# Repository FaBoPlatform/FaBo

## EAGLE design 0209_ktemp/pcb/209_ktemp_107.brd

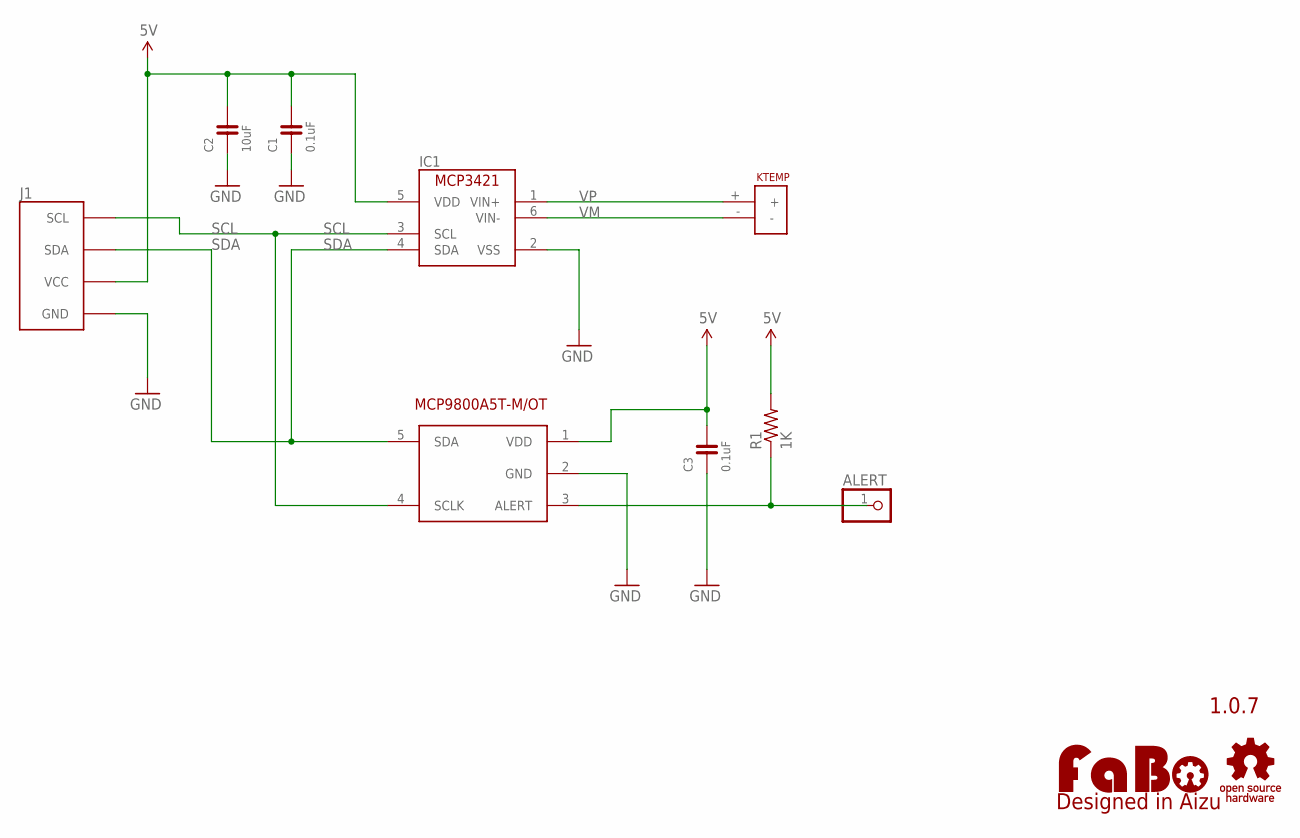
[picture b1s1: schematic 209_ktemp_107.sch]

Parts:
ALERT: PINHD-1X1; 1X01
C1, C3: 0.1uF; 0603
C2: 10uF; 0603
IC1: MCP3421; SOT-23
J1: FABO_BRICK_I2CI2C_TEMP_LOG2; FABO_BRICK_I2C_LONG2
LOGO1: LOGO_FABO-M; LOGO_FABO_M
R1: 1K; R0603
U$2: PCC-SMP-J
U$3: LOGO_OSHW-M_BOTTOM; LOGO_OSHW_M_BOTTOM
U$5: MCP9800_SOT-23; SOT23-5

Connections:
5V: C1.2, C2.2, C3.2, IC1.5 (VDD), J1.VCC, R1.2, U$5.1 (VDD)
GND: C1.1, C2.1, C3.1, IC1.2 (VSS), J1.GND, U$5.2 (GND)
unnamed: ALERT.1, R1.1, U$5.3 (ALERT)
SCL: IC1.3 (SCL), J1.SCL, U$5.4 (SCLK)
SDA: IC1.4 (SDA), J1.SDA, U$5.5 (SDA)
VM: IC1.6 (VIN-), U$2.-
VP: IC1.1 (VIN+), U$2.+

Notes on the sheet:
1.0.7

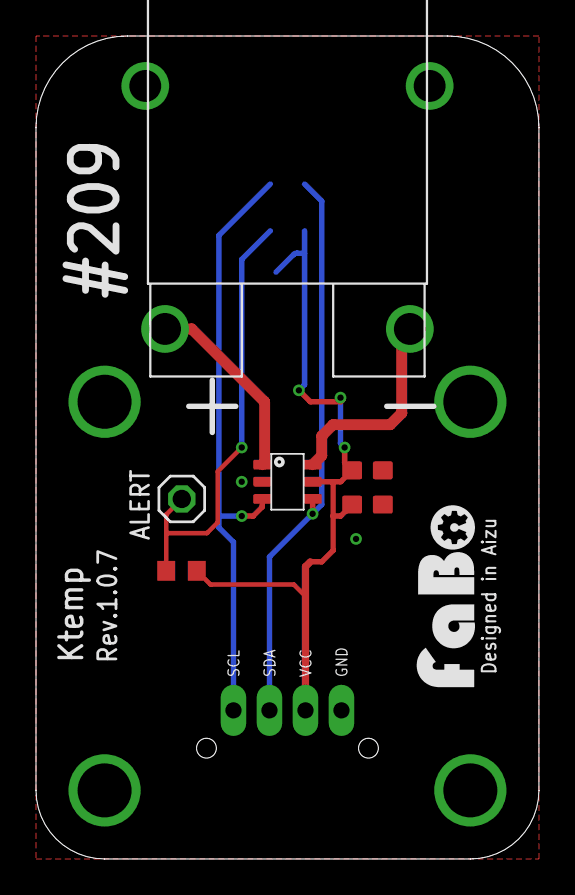
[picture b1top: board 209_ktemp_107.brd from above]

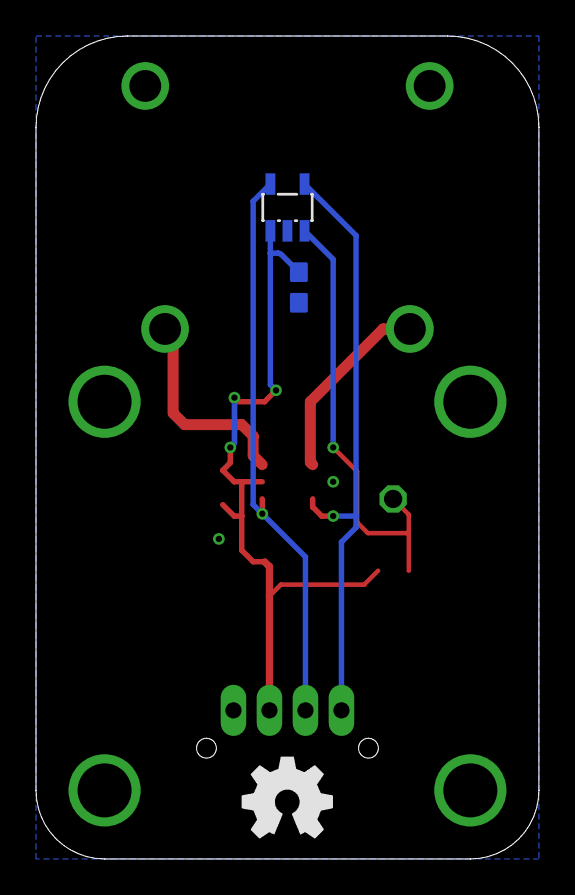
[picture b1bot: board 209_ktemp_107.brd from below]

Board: 2 copper layers, 27.9 x 45.7 mm, 11 parts (2 on the bottom side), 7 nets.

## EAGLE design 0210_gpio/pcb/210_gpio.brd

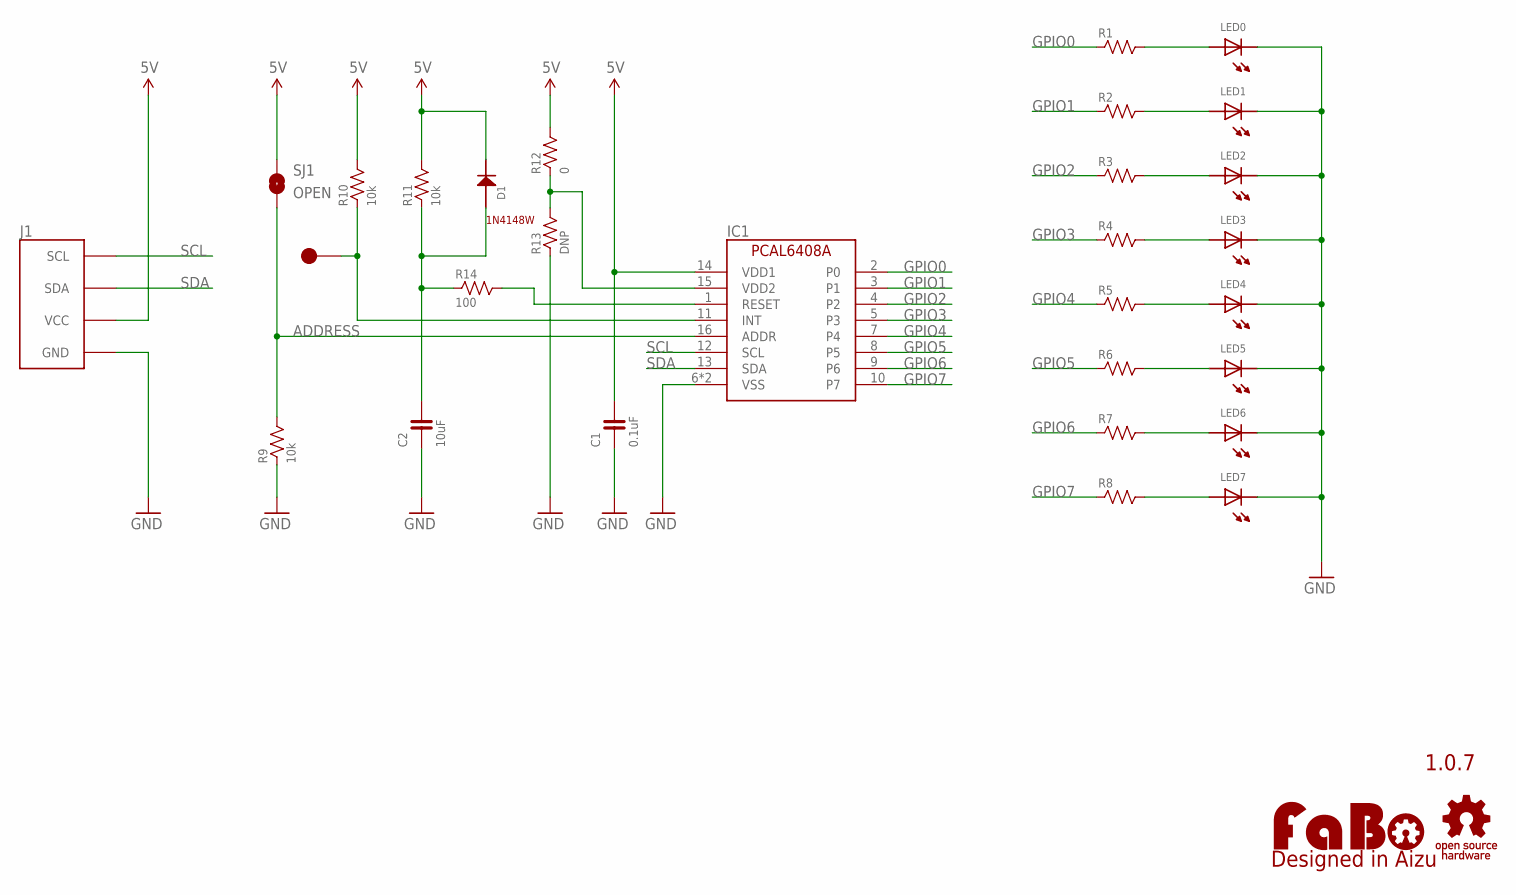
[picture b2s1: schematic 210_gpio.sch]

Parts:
C1: 0.1uF; 0603
C2: 10uF; 0805
D1: 1N4148; 1N4148W
IC1: NX-PCAL6408A; NXP-PCAL6408A
J1: FABO_BRICK_I2C
LED0, LED1, LED2, LED3, LED4, LED5, LED6, LED7: LED-0603-NARROW; 0603-NARROW
LOGO1: LOGO_FABO-M; LOGO_FABO_M
R1, R2, R3, R4, R5, R6, R7, R8: RESISTOR-0603-NARROW; 0603-NARROW
R9, R10, R11: 10k; 0603-NARROW
R12: 0; 0603-NARROW
R13: DNP; 0603-NARROW
R14: 100; 0603-NARROW
SJ1: OPEN; SMD-JUMPER-2-OPEN
TP1: TP-15
U$2: LOGO_OSHW-M_BOTTOM; LOGO_OSHW_M_BOTTOM

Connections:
5V: C1.2, D1.CATHODE, IC1.14 (VDD1), J1.VCC, R10.2, R11.2, R12.2, SJ1.1
ADDRESS: IC1.16 (ADDR), R9.2, SJ1.2
GND: C1.1, C2.1, IC1.6 (VSS), IC1.17 (VSS), J1.GND, LED0.CATHODE, LED1.CATHODE, LED2.CATHODE, LED3.CATHODE, LED4.CATHODE, LED5.CATHODE, LED6.CATHODE, LED7.CATHODE, R9.1, R13.1
GPIO0: IC1.2 (P0), R1.1
GPIO1: IC1.3 (P1), R2.1
GPIO2: IC1.4 (P2), R3.1
GPIO3: IC1.5 (P3), R4.1
GPIO4: IC1.7 (P4), R5.1
GPIO5: IC1.8 (P5), R6.1
GPIO6: IC1.9 (P6), R7.1
GPIO7: IC1.10 (P7), R8.1
unnamed: LED0.ANODE, R1.2
unnamed: LED1.ANODE, R2.2
unnamed: LED2.ANODE, R3.2
unnamed: LED3.ANODE, R4.2
unnamed: LED4.ANODE, R5.2
unnamed: LED5.ANODE, R6.2
unnamed: LED6.ANODE, R7.2
unnamed: LED7.ANODE, R8.2
unnamed: IC1.11 (INT), R10.1, TP1.1
unnamed: C2.2, D1.ANODE, R11.1, R14.1
unnamed: IC1.1 (RESET), R14.2
unnamed: IC1.15 (VDD2), R12.1, R13.2
SCL: IC1.12 (SCL), J1.SCL
SDA: IC1.13 (SDA), J1.SDA

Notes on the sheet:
1.0.7
1N4148W

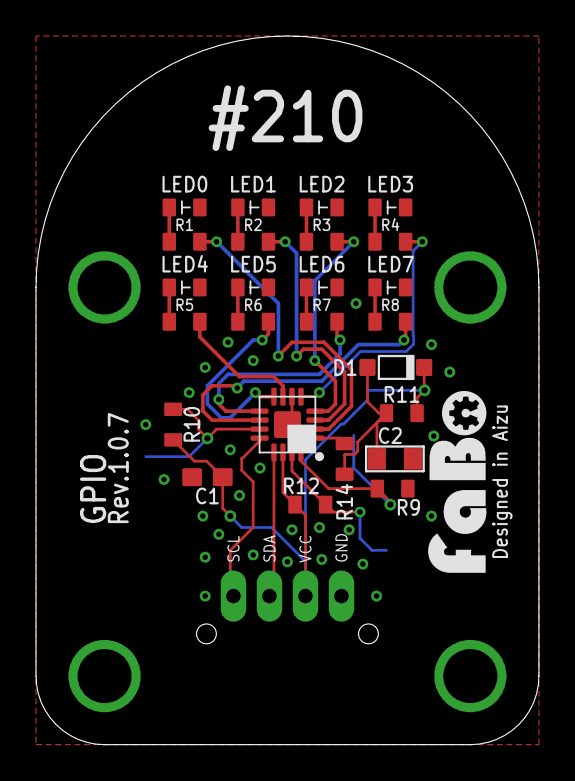
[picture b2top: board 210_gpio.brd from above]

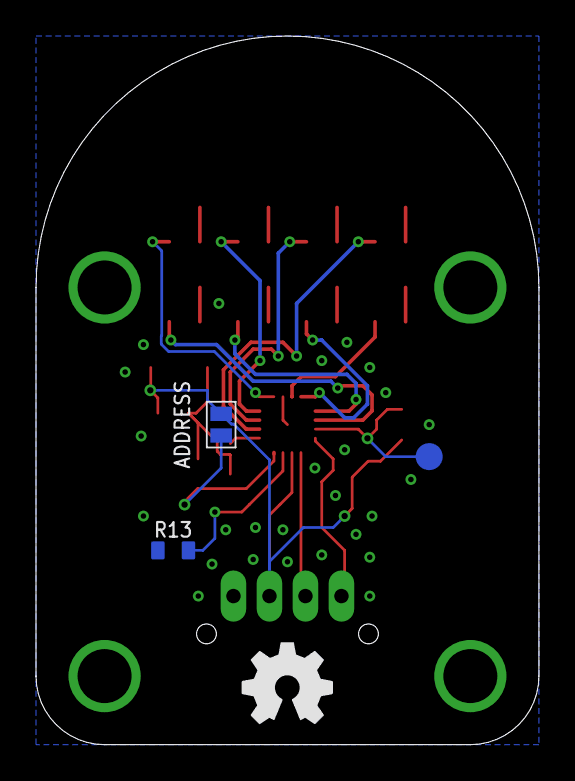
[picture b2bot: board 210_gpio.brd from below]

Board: 2 copper layers, 27.9 x 39.4 mm, 31 parts (3 on the bottom side), 25 nets.

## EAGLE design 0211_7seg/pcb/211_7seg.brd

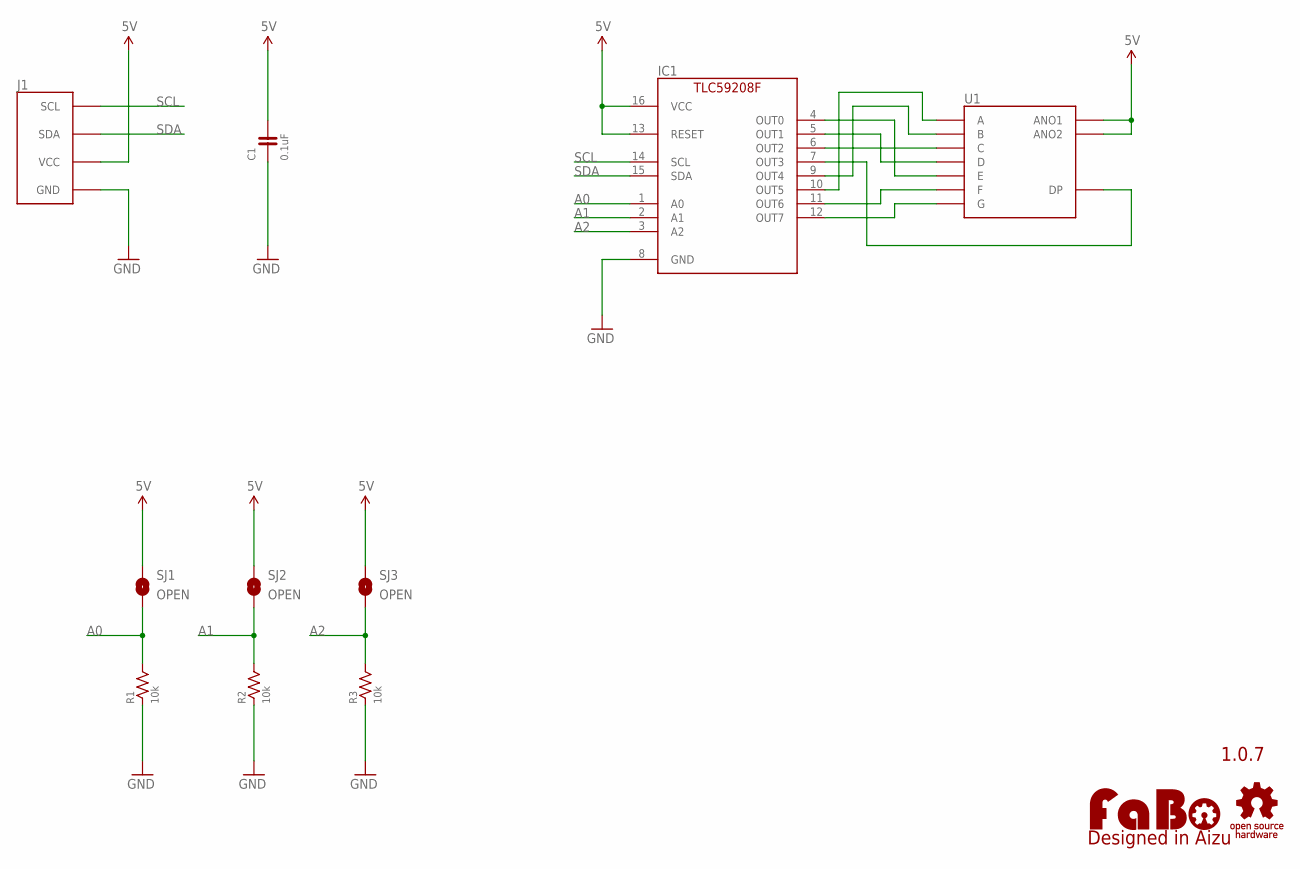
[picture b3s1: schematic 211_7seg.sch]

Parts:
C1: 0.1uF; 0603
IC1: TLC59208FIPWR; TSSOP16
J1: FABO_BRICK_I2C
LOGO1: LOGO_FABO-M; LOGO_FABO_M
R1, R2, R3: 10k; 0603
SJ1, SJ2, SJ3: OPEN; SMD-JUMPER-2-OPEN
U1: 7SEG_ANO; A-551SRD
U$2: LOGO_OSHW-M_BOTTOM; LOGO_OSHW_M_BOTTOM

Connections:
5V: C1.2, IC1.13 (RESET), IC1.16 (VCC), J1.VCC, SJ1.1, SJ2.1, SJ3.1, U1.ANO1, U1.ANO2
A0: IC1.1 (A0), R1.2, SJ1.2
A1: IC1.2 (A1), R2.2, SJ2.2
A2: IC1.3 (A2), R3.2, SJ3.2
GND: C1.1, IC1.8 (GND), J1.GND, R1.1, R2.1, R3.1
unnamed: IC1.4 (OUT0), U1.E
unnamed: IC1.5 (OUT1), U1.D
unnamed: IC1.6 (OUT2), U1.C
unnamed: IC1.7 (OUT3), U1.DP
unnamed: IC1.9 (OUT4), U1.B
unnamed: IC1.10 (OUT5), U1.A
unnamed: IC1.11 (OUT6), U1.F
unnamed: IC1.12 (OUT7), U1.G
SCL: IC1.14 (SCL), J1.SCL
SDA: IC1.15 (SDA), J1.SDA

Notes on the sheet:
1.0.7

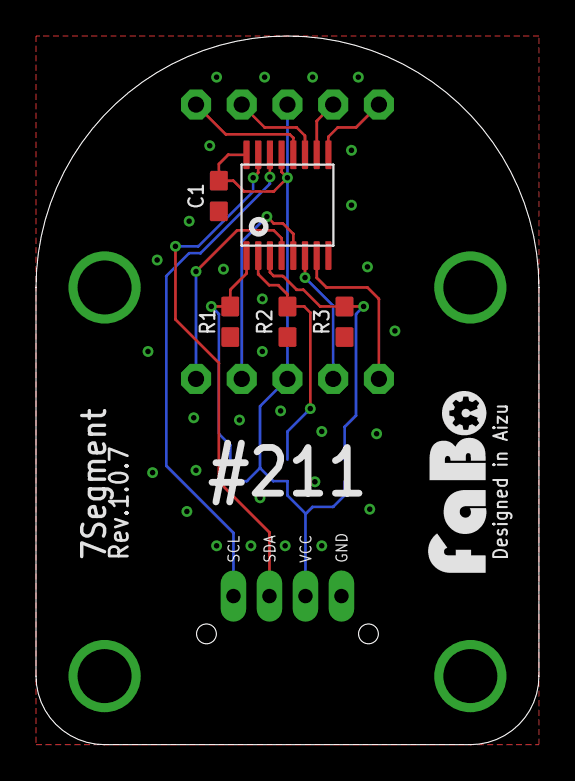
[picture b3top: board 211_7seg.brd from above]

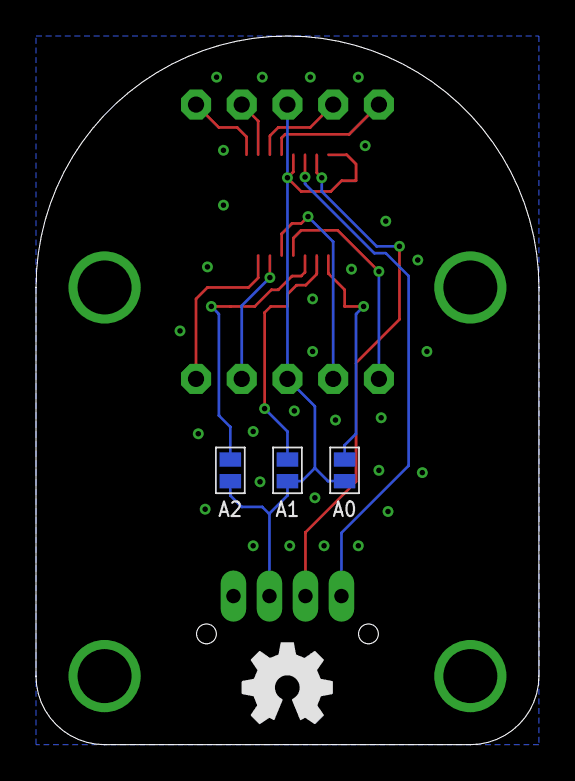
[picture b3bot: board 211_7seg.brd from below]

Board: 2 copper layers, 27.9 x 39.4 mm, 12 parts (3 on the bottom side), 15 nets.

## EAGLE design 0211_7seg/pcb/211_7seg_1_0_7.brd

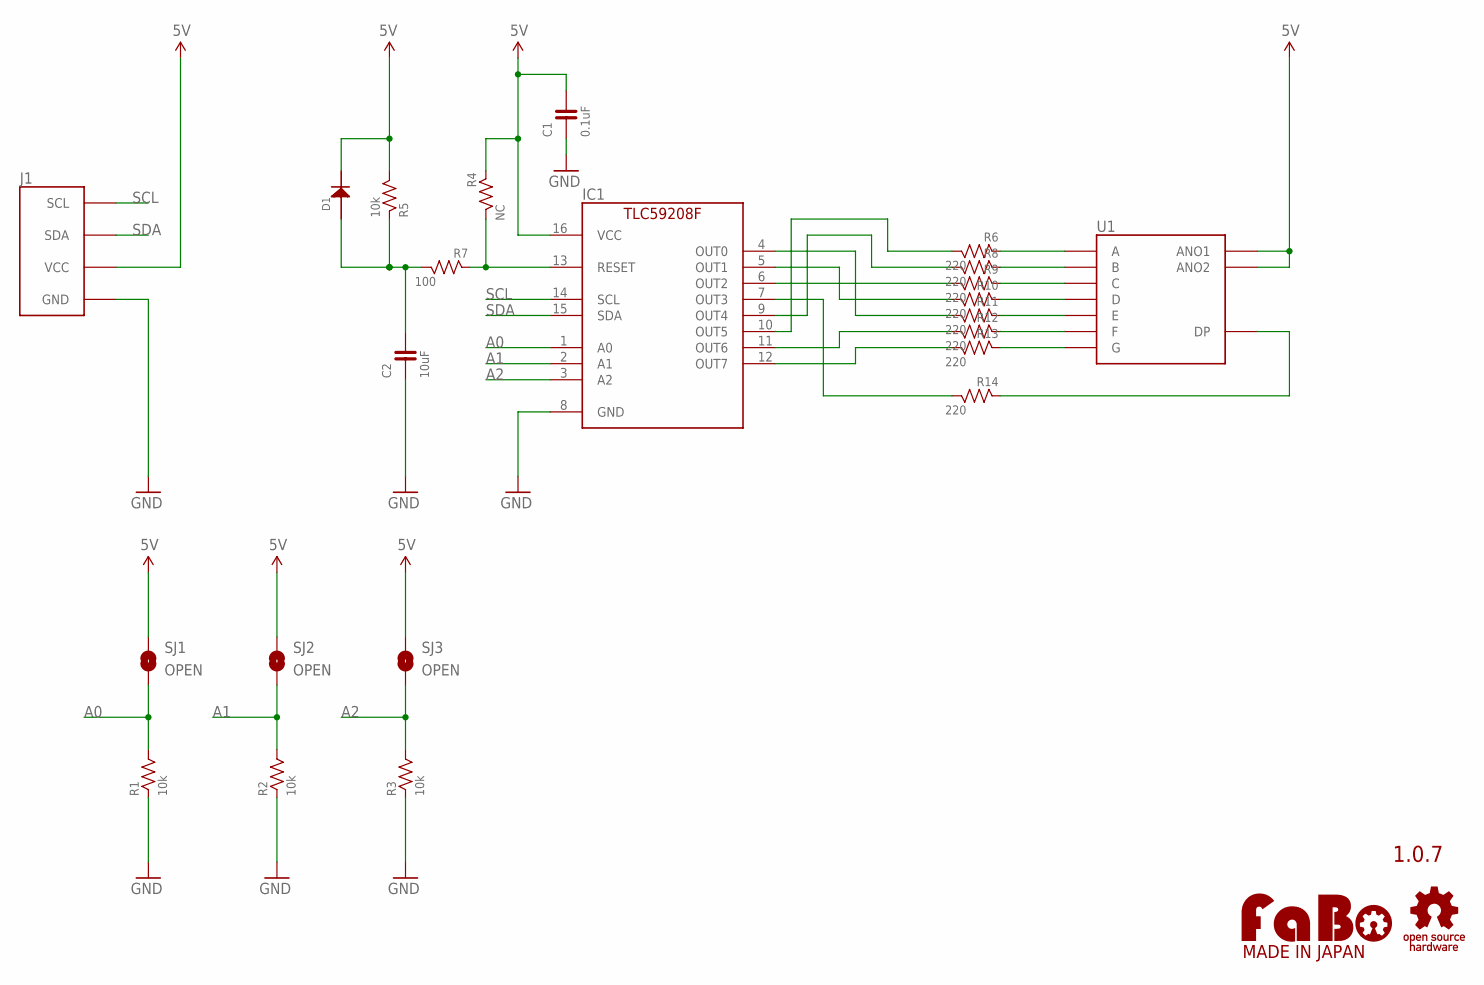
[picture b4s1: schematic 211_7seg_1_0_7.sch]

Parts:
C1: 0.1uF; 0603
C2: 10uF; 0603
D1: 1N4148; 1N4148W
IC1: TLC59208FIPWR; TSSOP16
J1: FABO_BRICK_I2C
R1, R2, R3, R5: 10k; 0603
R4: NC; 0603
R6, R8, R9, R10, R11, R12, R13, R14: 220; 0603
R7: 100; 0603
SJ1, SJ2, SJ3: OPEN; SMD-JUMPER-2-OPEN
U1: 7SEG_ANO; A-551SRD
U$2: LOGO_OSHW-M_BOTTOM; LOGO_OSHW_M_BOTTOM
U$4: LOGO_FABO-M; LOGO_FABO_MS

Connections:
5V: C1.2, D1.CATHODE, IC1.16 (VCC), J1.VCC, R4.1, R5.2, SJ1.1, SJ2.1, SJ3.1, U1.ANO1, U1.ANO2
A0: IC1.1 (A0), R1.2, SJ1.2
A1: IC1.2 (A1), R2.2, SJ2.2
A2: IC1.3 (A2), R3.2, SJ3.2
GND: C1.1, C2.1, IC1.8 (GND), J1.GND, R1.1, R2.1, R3.1
unnamed: IC1.4 (OUT0), R11.2
unnamed: IC1.5 (OUT1), R10.2
unnamed: R9.1, U1.C
unnamed: IC1.7 (OUT3), R14.2
unnamed: IC1.9 (OUT4), R8.2
unnamed: IC1.10 (OUT5), R6.2
unnamed: IC1.11 (OUT6), R12.2
unnamed: IC1.12 (OUT7), R13.2
unnamed: C2.2, D1.ANODE, R5.1, R7.2
unnamed: IC1.13 (RESET), R4.2, R7.1
unnamed: R6.1, U1.A
unnamed: R8.1, U1.B
unnamed: IC1.6 (OUT2), R9.2
unnamed: R10.1, U1.D
unnamed: R11.1, U1.E
unnamed: R12.1, U1.F
unnamed: R13.1, U1.G
unnamed: R14.1, U1.DP
SCL: IC1.14 (SCL), J1.SCL
SDA: IC1.15 (SDA), J1.SDA

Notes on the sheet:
1.0.7

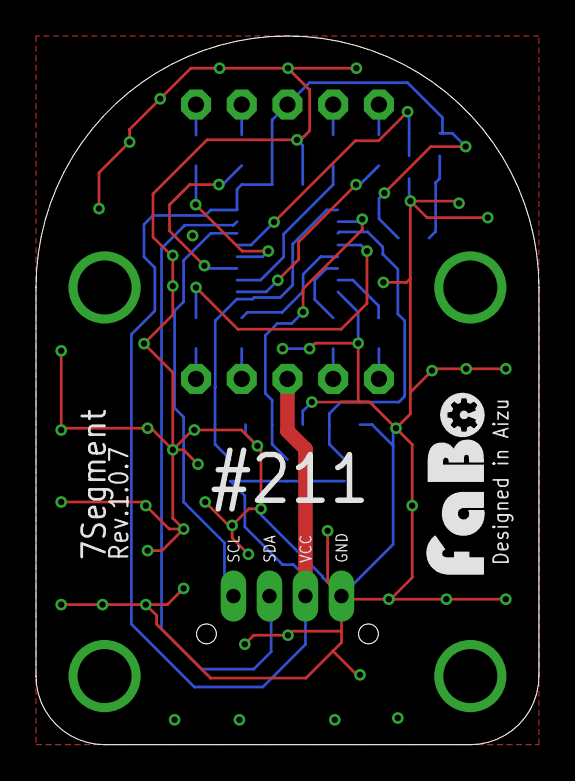
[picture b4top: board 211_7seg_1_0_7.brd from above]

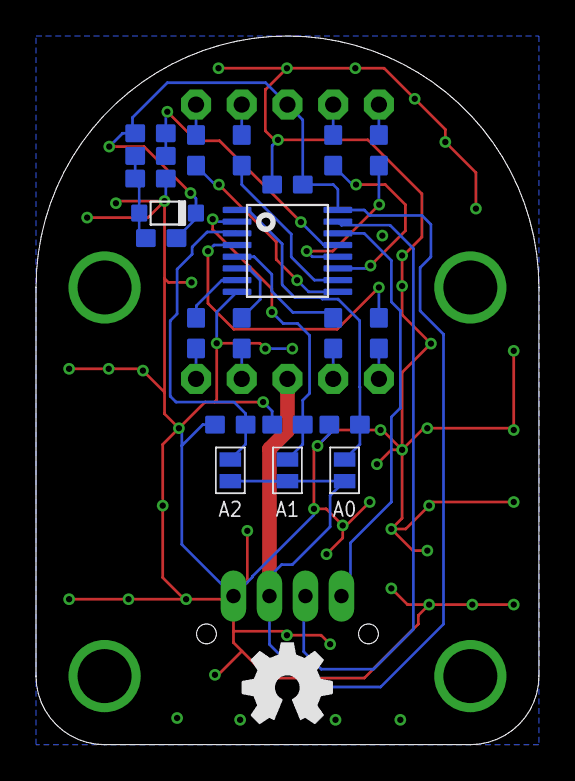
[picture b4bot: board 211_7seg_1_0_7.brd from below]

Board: 2 copper layers, 27.9 x 39.4 mm, 25 parts (21 on the bottom side), 25 nets.

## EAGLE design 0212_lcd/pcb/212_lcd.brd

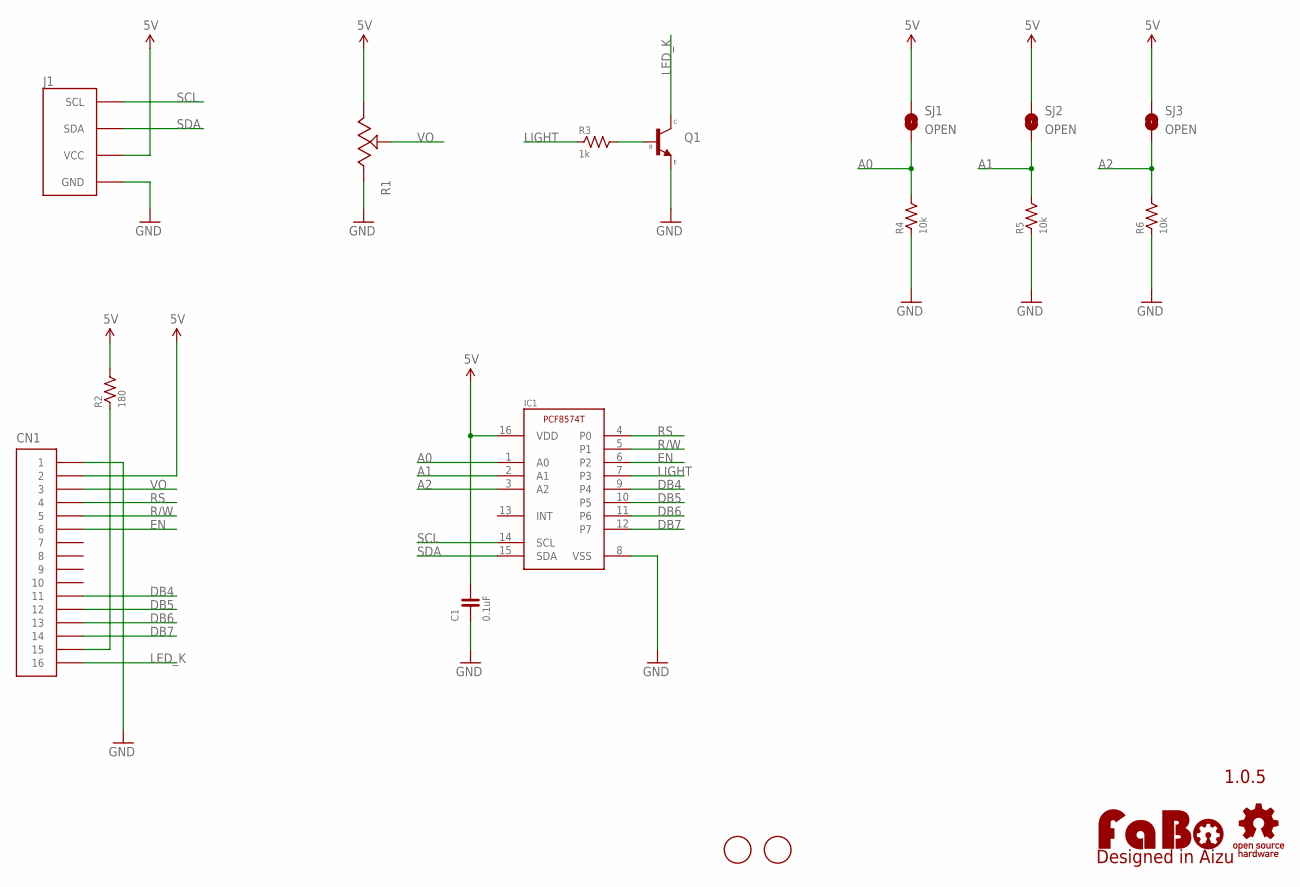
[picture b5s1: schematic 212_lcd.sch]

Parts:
C1: 0.1uF; 0603
CN1: PIN_HEADER_1X16-LONG; PIN_1X16_LONG
IC1: PCF8574T; SO16
J1: FABO_BRICK_I2C-S04B-PASK-2_LONG; FABO_BRICK_I2C_S04B-PASK-2_LONG
LOGO1: LOGO_FABO-M; LOGO_FABO_M
Q1: NPN-SMD; SOT23
R1: RESISTOR_VARIABLE-SMD; TC33X
R2: 180; 0603
R3: 1k; 0603
R4, R5, R6: 10k; 0603
SJ1, SJ2, SJ3: OPEN; SMD-JUMPER-2-OPEN
U$2: LOGO_OSHW-M_BOTTOM; LOGO_OSHW_M_BOTTOM
U$4, U$5: SCREW-PAD-3MM; SCREWPAD_3MM

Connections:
5V: C1.2, CN1.2, IC1.16 (VDD), J1.VCC, R1.1, R2.2, SJ1.1, SJ2.1, SJ3.1
A0: IC1.1 (A0), R4.2, SJ1.2
A1: IC1.2 (A1), R5.2, SJ2.2
A2: IC1.3 (A2), R6.2, SJ3.2
BASE: Q1.1 (B), R3.2
DB4: CN1.11, IC1.9 (P4)
DB5: CN1.12, IC1.10 (P5)
DB6: CN1.13, IC1.11 (P6)
DB7: CN1.14, IC1.12 (P7)
EN: CN1.6, IC1.6 (P2)
GND: C1.1, CN1.1, IC1.8 (VSS), J1.GND, Q1.2 (E), R1.3, R4.1, R5.1, R6.1
LED_A: CN1.15, R2.1
LED_K: CN1.16, Q1.3 (C)
LIGHT: IC1.7 (P3), R3.1
R/W: CN1.5, IC1.5 (P1)
RS: CN1.4, IC1.4 (P0)
SCL: IC1.14 (SCL), J1.SCL
SDA: IC1.15 (SDA), J1.SDA
VO: CN1.3, R1.2

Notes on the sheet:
1.0.5

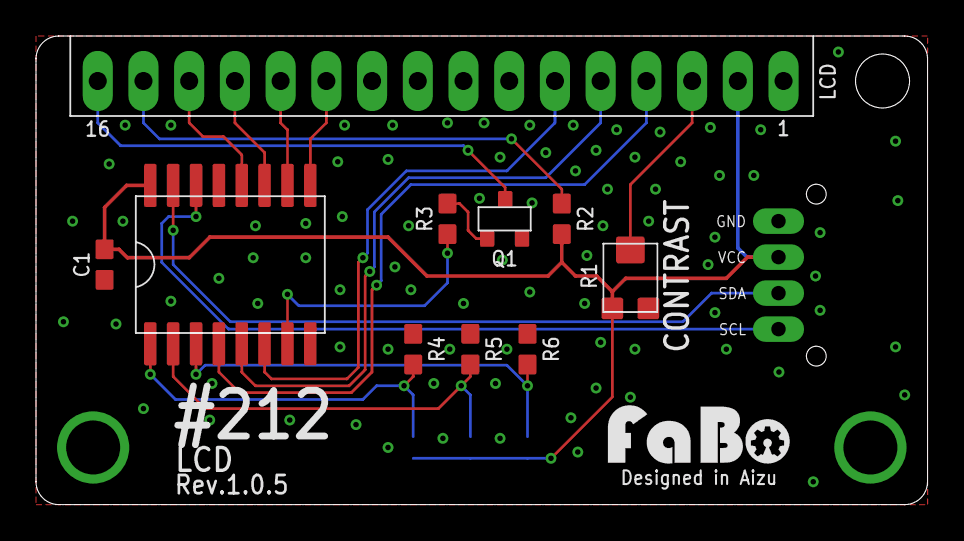
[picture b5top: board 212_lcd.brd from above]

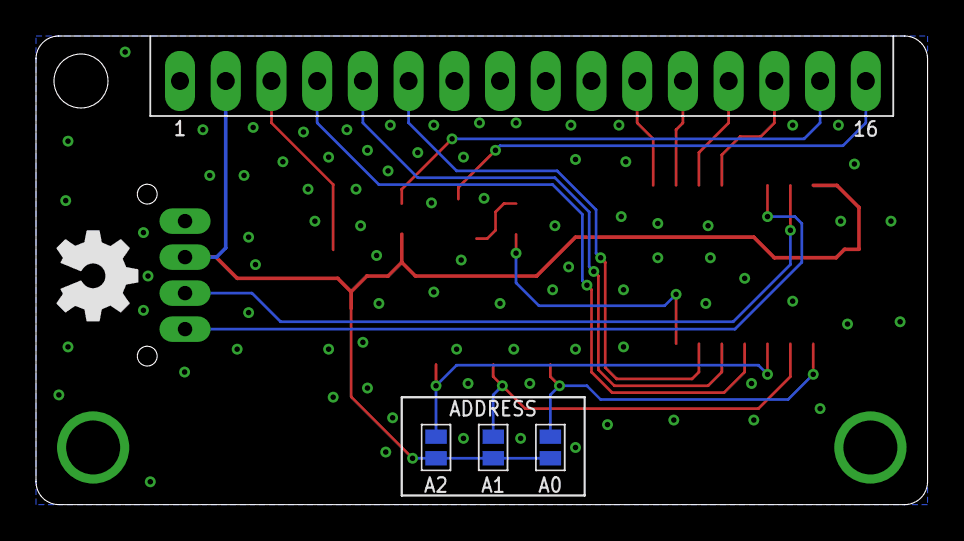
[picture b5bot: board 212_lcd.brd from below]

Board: 2 copper layers, 49.5 x 26.0 mm, 18 parts (3 on the bottom side), 19 nets.

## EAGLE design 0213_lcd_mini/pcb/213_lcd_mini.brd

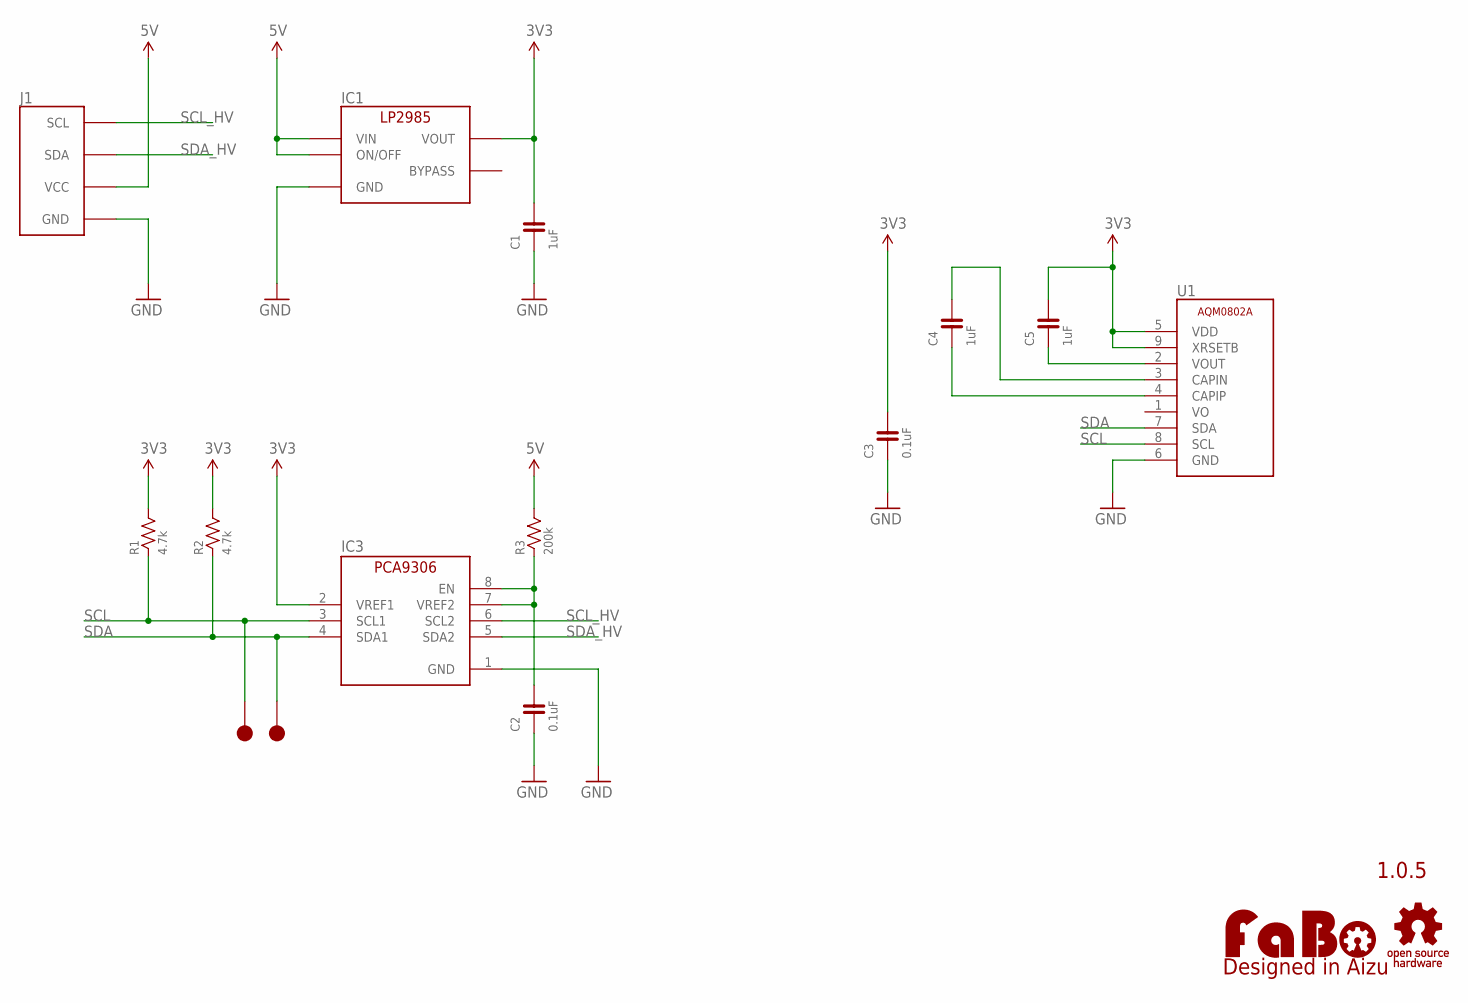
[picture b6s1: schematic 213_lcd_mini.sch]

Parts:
C1, C4, C5: 1uF; 0603
C2, C3: 0.1uF; 0603
IC1: LP2985-33DBV; SOT-23-5
IC3: PCA9306GM; XQFN8
J1: FABO_BRICK_I2C
LOGO1: LOGO_FABO-M; LOGO_FABO_M
R1, R2: 4.7k; 0603
R3: 200k; 0603
TP1, TP2: TP-15
U1: AQM0802A
U$2: LOGO_OSHW-M_BOTTOM; LOGO_OSHW_M_BOTTOM

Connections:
3V3: C1.2, C3.2, C5.2, IC1.5 (VOUT), IC3.2 (VREF1), R1.2, R2.2, U1.5 (VDD), U1.9 (XRSETB)
5V: IC1.1 (VIN), IC1.3 (ON/OFF), J1.VCC, R3.2
CAPIN: C4.2, U1.3 (CAPIN)
CAPIP: C4.1, U1.4 (CAPIP)
GND: C1.1, C2.1, C3.1, IC1.2 (GND), IC3.1 (GND), J1.GND, U1.6 (GND)
unnamed: C2.2, IC3.7 (VREF2), IC3.8 (EN), R3.1
SCL: IC3.3 (SCL1), R1.1, TP2.1, U1.8 (SCL)
SCL_HV: IC3.6 (SCL2), J1.SCL
SDA: IC3.4 (SDA1), R2.1, TP1.1, U1.7 (SDA)
SDA_HV: IC3.5 (SDA2), J1.SDA
VOUT: C5.1, U1.2 (VOUT)

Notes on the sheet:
1.0.5

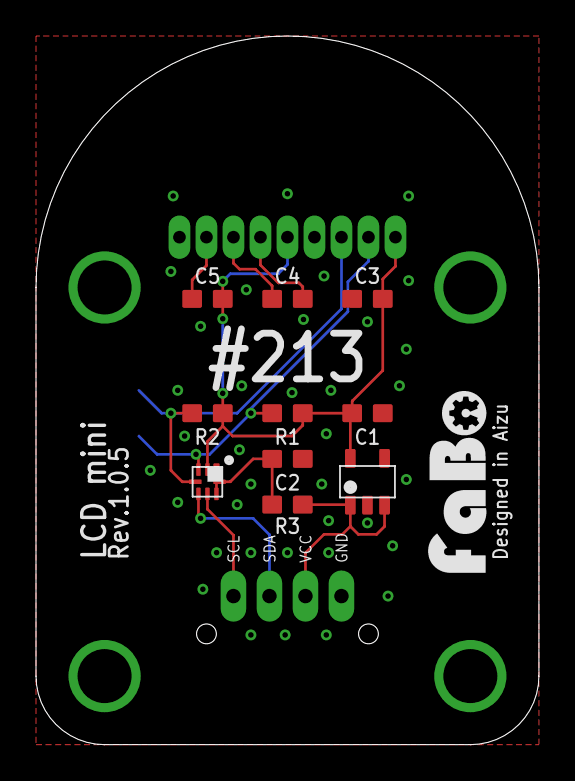
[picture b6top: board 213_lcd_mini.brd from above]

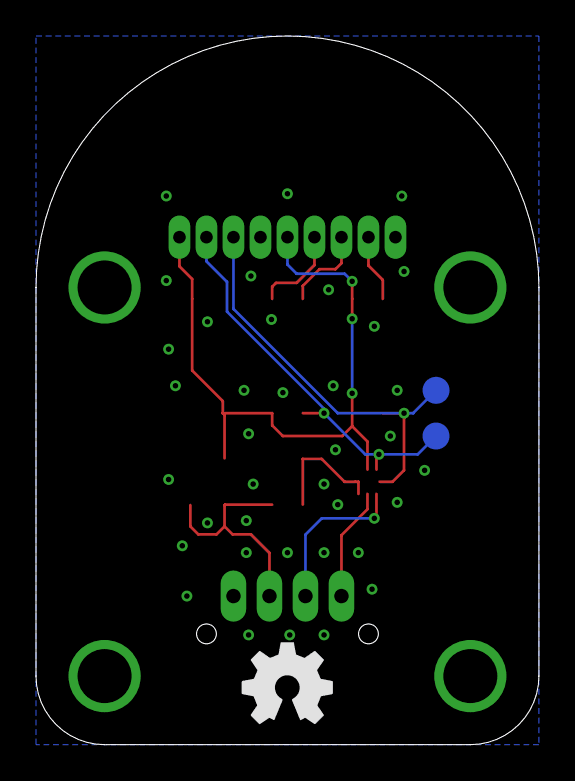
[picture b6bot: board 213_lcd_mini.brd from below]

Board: 2 copper layers, 27.9 x 39.4 mm, 16 parts (2 on the bottom side), 11 nets.

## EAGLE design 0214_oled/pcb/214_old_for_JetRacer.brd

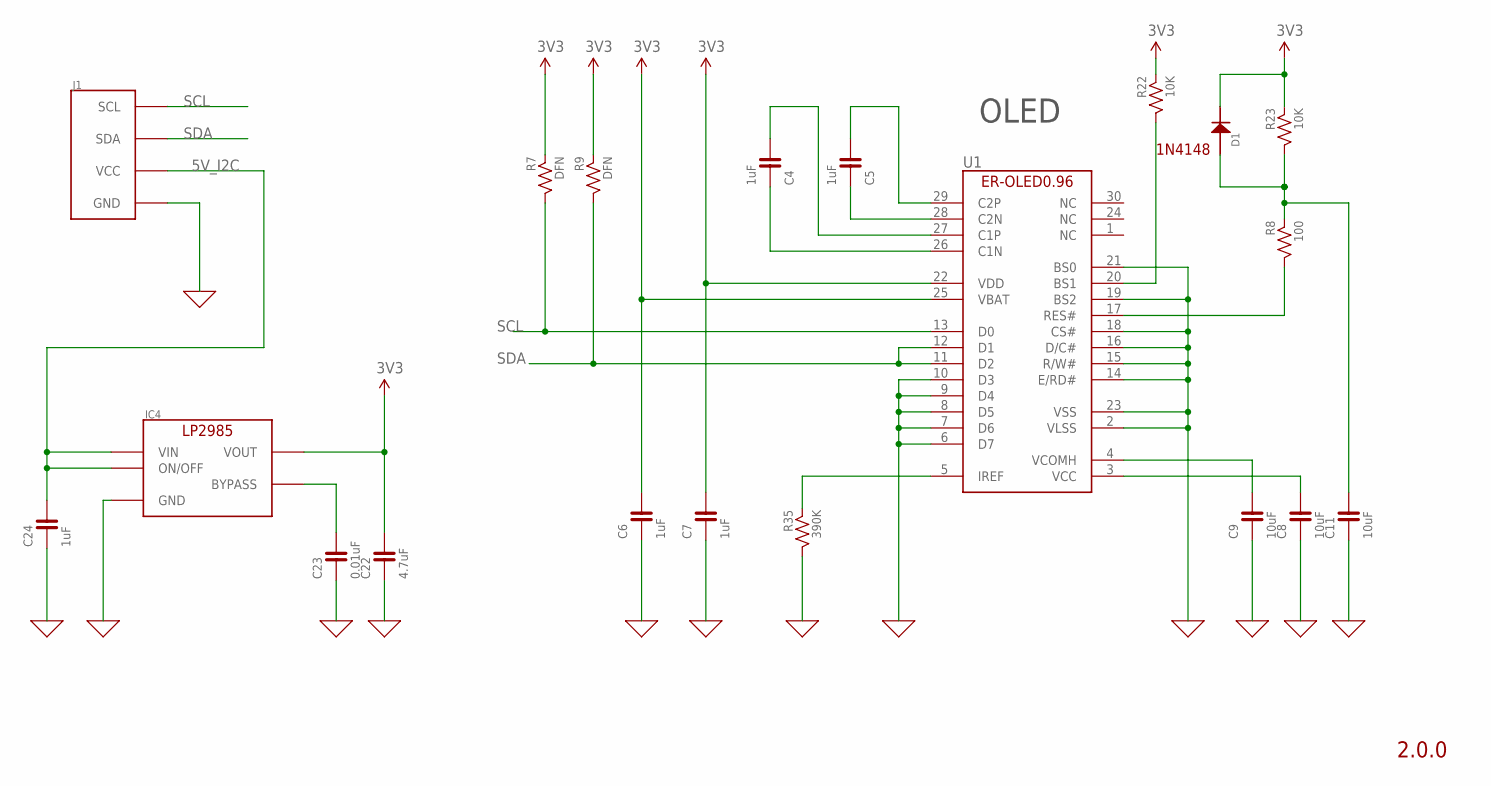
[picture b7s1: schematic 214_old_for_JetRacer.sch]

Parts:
C4, C5, C6, C7, C24: 1uF; 0603
C8, C9, C11: 10uF; 0603
C22: 4.7uF; 0603
C23: 0.01uF; 0603
D1: 1N4148; 1N4148W
IC4: LP2985-33DBV; SOT-23-5
J1: FABO_BRICK_I2C-S04B-PASK-2; FABO_BRICK_I2C_S04B-PASK-2
R7, R9: DFN; 0603
R8: 100; 0603
R22, R23: 10K; 0603
R35: 390K; 0603
U1: ER-OLED0.96-1ER-CON30HT-1; ER-CON30HT-1

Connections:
0: C6.1, C7.1, C8.1, C9.1, C11.1, C22.1, C23.1, C24.1, IC4.2 (GND), J1.GND, R35.2, U1.2 (VLSS), U1.6 (D7), U1.7 (D6), U1.8 (D5), U1.9 (D4), U1.10 (D3), U1.14 (E/RD#), U1.15 (R/W#), U1.16 (D/C#), U1.18 (CS#), U1.19 (BS2), U1.21 (BS0), U1.23 (VSS)
3V3: C6.2, C7.2, C22.2, D1.CATHODE, IC4.5 (VOUT), R7.1, R9.1, R22.1, R23.1, U1.22 (VDD), U1.25 (VBAT)
5V_I2C: C24.2, IC4.1 (VIN), IC4.3 (ON/OFF), J1.VCC
unnamed: C23.2, IC4.4 (BYPASS)
unnamed: C4.2, U1.27 (C1P)
unnamed: C4.1, U1.26 (C1N)
unnamed: C5.1, U1.28 (C2N)
unnamed: C5.2, U1.29 (C2P)
unnamed: R35.1, U1.5 (IREF)
unnamed: C9.2, U1.4 (VCOMH)
unnamed: C8.2, U1.3 (VCC)
unnamed: R8.2, U1.17 (RES#)
unnamed: C11.2, D1.ANODE, R8.1, R23.2
unnamed: R22.2, U1.20 (BS1)
SCL: J1.SCL, R7.2, U1.13 (D0)
SDA: J1.SDA, R9.2, U1.11 (D2), U1.12 (D1)

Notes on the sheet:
1N4148
OLED
2.0.0

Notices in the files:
parts and their libraries:
FaBo-etc: Released under the Creative Commons Attribution-ShareAlike 4.0 License
https://creativecommons.org/licenses/by-sa/4.0
FaBo-etc: Released under the Creative Commons
